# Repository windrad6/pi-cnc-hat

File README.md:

https://www.digikey.de/de/products/detail/edac-inc/630-025-640-541/10867386

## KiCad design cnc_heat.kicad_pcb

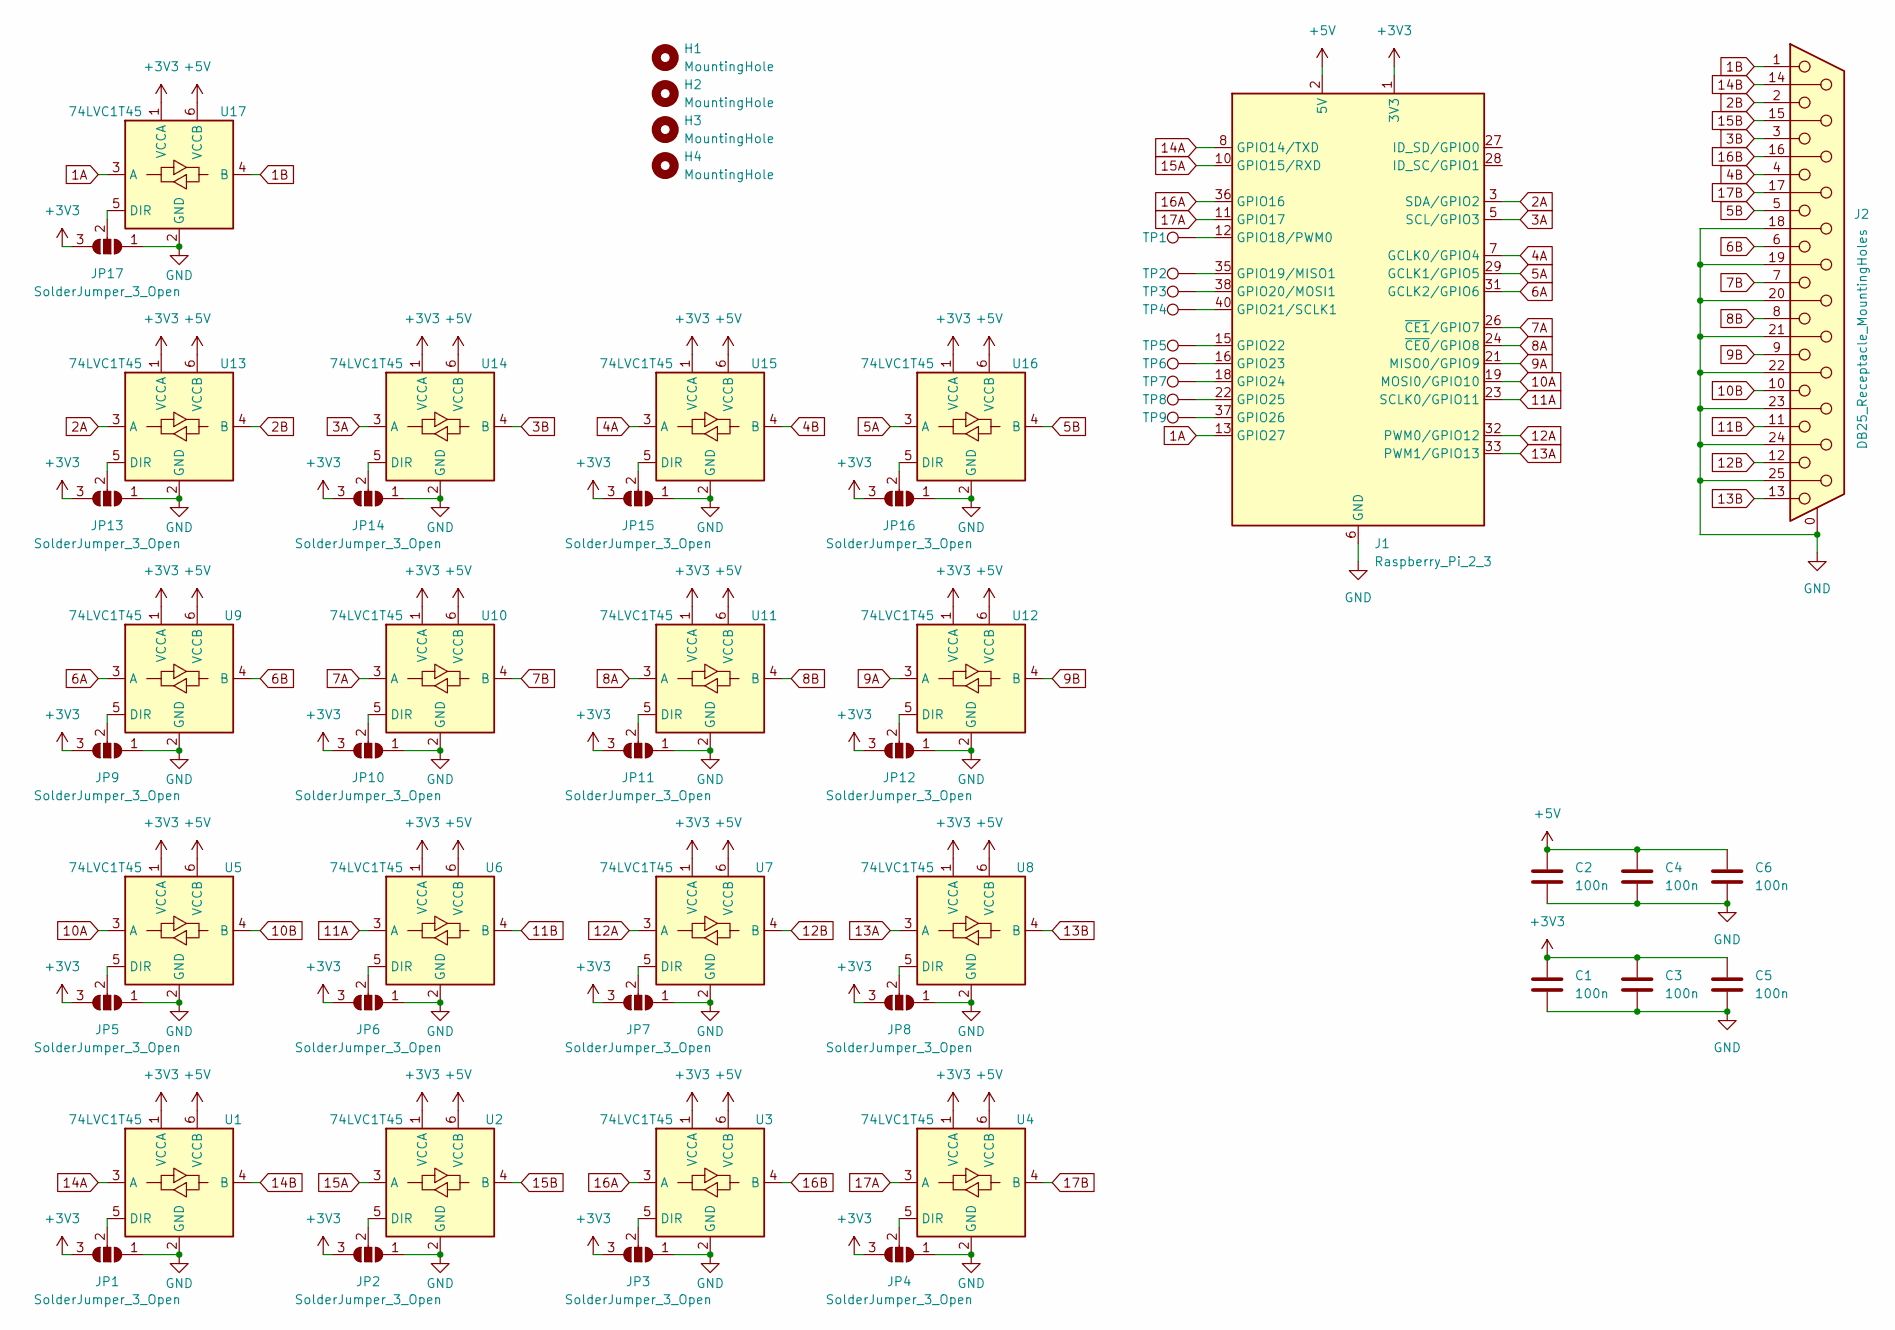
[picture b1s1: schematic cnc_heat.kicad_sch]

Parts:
C1, C2, C3, C4, C5, C6: 100n; C_1206_3216Metric_Pad1.33x1.80mm_HandSolder
H1, H2, H3, H4: MountingHole; MountingHole_2.7mm_M2.5
J1: Raspberry_Pi_2_3; PinSocket_2x20_P2.54mm_Vertical
J2: DB25_Receptacle_MountingHoles; DSUB-25_Female_Horizontal_P2.77x2.84mm_EdgePinOffset9.90mm_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; DIGIKEY 151-630-025-640-541-ND
JP1, JP2, JP3, JP4, JP5, JP6, JP7, JP8, JP9, JP10, JP11, JP12, JP13, JP14, JP15, JP16, JP17: SolderJumper_3_Open; SolderJumper-3_P2.0mm_Open_TrianglePad1.0x1.5mm_NumberLabels
TP1, TP2, TP3, TP4, TP5, TP6, TP7, TP8, TP9: TestPoint; TestPoint_Pad_1.5x1.5mm
U1, U2, U3, U4, U5, U6, U7, U8, U9, U10, U11, U12, U13, U14, U15, U16, U17: 74LVC1T45; SOT-23-6; DIGIKEY 74LVC1T45W6-7

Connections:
1A: J1.13 (GPIO27), U17.3 (A)
1B: J2.1, U17.4 (B)
2A: J1.3 (SDA/GPIO2), U13.3 (A)
2B: J2.2, U13.4 (B)
3A: J1.5 (SCL/GPIO3), U14.3 (A)
3B: J2.3, U14.4 (B)
4A: J1.7 (GCLK0/GPIO4), U15.3 (A)
4B: J2.4, U15.4 (B)
5A: J1.29 (GCLK1/GPIO5), U16.3 (A)
5B: J2.5, U16.4 (B)
6A: J1.31 (GCLK2/GPIO6), U9.3 (A)
6B: J2.6, U9.4 (B)
7A: J1.26 (~CE1/GPIO7), U10.3 (A)
7B: J2.7, U10.4 (B)
8A: J1.24 (~CE0/GPIO8), U11.3 (A)
8B: J2.8, U11.4 (B)
9A: J1.21 (MISO0/GPIO9), U12.3 (A)
9B: J2.9, U12.4 (B)
10A: J1.19 (MOSI0/GPIO10), U5.3 (A)
10B: J2.10, U5.4 (B)
11A: J1.23 (SCLK0/GPIO11), U6.3 (A)
11B: J2.11, U6.4 (B)
12A: J1.32 (PWM0/GPIO12), U7.3 (A)
12B: J2.12, U7.4 (B)
13A: J1.33 (PWM1/GPIO13), U8.3 (A)
13B: J2.13, U8.4 (B)
14A: J1.8 (GPIO14/TXD), U1.3 (A)
14B: J2.14, U1.4 (B)
15A: J1.10 (GPIO15/RXD), U2.3 (A)
15B: J2.15, U2.4 (B)
16A: J1.36 (GPIO16), U3.3 (A)
16B: J2.16, U3.4 (B)
17A: J1.11 (GPIO17), U4.3 (A)
17B: J2.17, U4.4 (B)
+3V3: C1.1, C3.1, C5.1, J1.1 (3V3), J1.17 (3V3), JP1.3 (B), JP2.3 (B), JP3.3 (B), JP4.3 (B), JP5.3 (B), JP6.3 (B), JP7.3 (B), JP8.3 (B), JP9.3 (B), JP10.3 (B), JP11.3 (B), JP12.3 (B), JP13.3 (B), JP14.3 (B), JP15.3 (B), JP16.3 (B), JP17.3 (B), U1.1 (VCCA), U2.1 (VCCA), U3.1 (VCCA), U4.1 (VCCA), U5.1 (VCCA), U6.1 (VCCA), U7.1 (VCCA), U8.1 (VCCA), U9.1 (VCCA), U10.1 (VCCA), U11.1 (VCCA), U12.1 (VCCA), U13.1 (VCCA), U14.1 (VCCA), U15.1 (VCCA), U16.1 (VCCA), U17.1 (VCCA)
+5V: C2.1, C4.1, C6.1, J1.2 (5V), J1.4 (5V), U1.6 (VCCB), U2.6 (VCCB), U3.6 (VCCB), U4.6 (VCCB), U5.6 (VCCB), U6.6 (VCCB), U7.6 (VCCB), U8.6 (VCCB), U9.6 (VCCB), U10.6 (VCCB), U11.6 (VCCB), U12.6 (VCCB), U13.6 (VCCB), U14.6 (VCCB), U15.6 (VCCB), U16.6 (VCCB), U17.6 (VCCB)
GND: C1.2, C2.2, C3.2, C4.2, C5.2, C6.2, J1.6 (GND), J1.9 (GND), J1.14 (GND), J1.20 (GND), J1.25 (GND), J1.30 (GND), J1.34 (GND), J1.39 (GND), J2.0 (PAD), J2.18, J2.19, J2.20, J2.21, J2.22, J2.23, J2.24, J2.25, JP1.1 (A), JP2.1 (A), JP3.1 (A), JP4.1 (A), JP5.1 (A), JP6.1 (A), JP7.1 (A), JP8.1 (A), JP9.1 (A), JP10.1 (A), JP11.1 (A), JP12.1 (A), JP13.1 (A), JP14.1 (A), JP15.1 (A), JP16.1 (A), JP17.1 (A), U1.2 (GND), U2.2 (GND), U3.2 (GND), U4.2 (GND), U5.2 (GND), U6.2 (GND), U7.2 (GND), U8.2 (GND), U9.2 (GND), U10.2 (GND), U11.2 (GND), U12.2 (GND), U13.2 (GND), U14.2 (GND), U15.2 (GND), U16.2 (GND), U17.2 (GND)
unnamed: J1.12 (GPIO18/PWM0), TP1.1
unnamed: J1.35 (GPIO19/MISO1), TP2.1
unnamed: J1.38 (GPIO20/MOSI1), TP3.1
unnamed: J1.40 (GPIO21/SCLK1), TP4.1
unnamed: J1.15 (GPIO22), TP5.1
unnamed: J1.16 (GPIO23), TP6.1
unnamed: J1.18 (GPIO24), TP7.1
unnamed: J1.22 (GPIO25), TP8.1
unnamed: J1.37 (GPIO26), TP9.1
unnamed: JP1.2 (C), U1.5 (DIR)
unnamed: JP2.2 (C), U2.5 (DIR)
unnamed: JP3.2 (C), U3.5 (DIR)
unnamed: JP4.2 (C), U4.5 (DIR)
unnamed: JP5.2 (C), U5.5 (DIR)
unnamed: JP6.2 (C), U6.5 (DIR)
unnamed: JP7.2 (C), U7.5 (DIR)
unnamed: JP8.2 (C), U8.5 (DIR)
unnamed: JP9.2 (C), U9.5 (DIR)
unnamed: JP10.2 (C), U10.5 (DIR)
unnamed: JP11.2 (C), U11.5 (DIR)
unnamed: JP12.2 (C), U12.5 (DIR)
unnamed: JP13.2 (C), U13.5 (DIR)
unnamed: JP14.2 (C), U14.5 (DIR)
unnamed: JP15.2 (C), U15.5 (DIR)
unnamed: JP16.2 (C), U16.5 (DIR)
unnamed: JP17.2 (C), U17.5 (DIR)

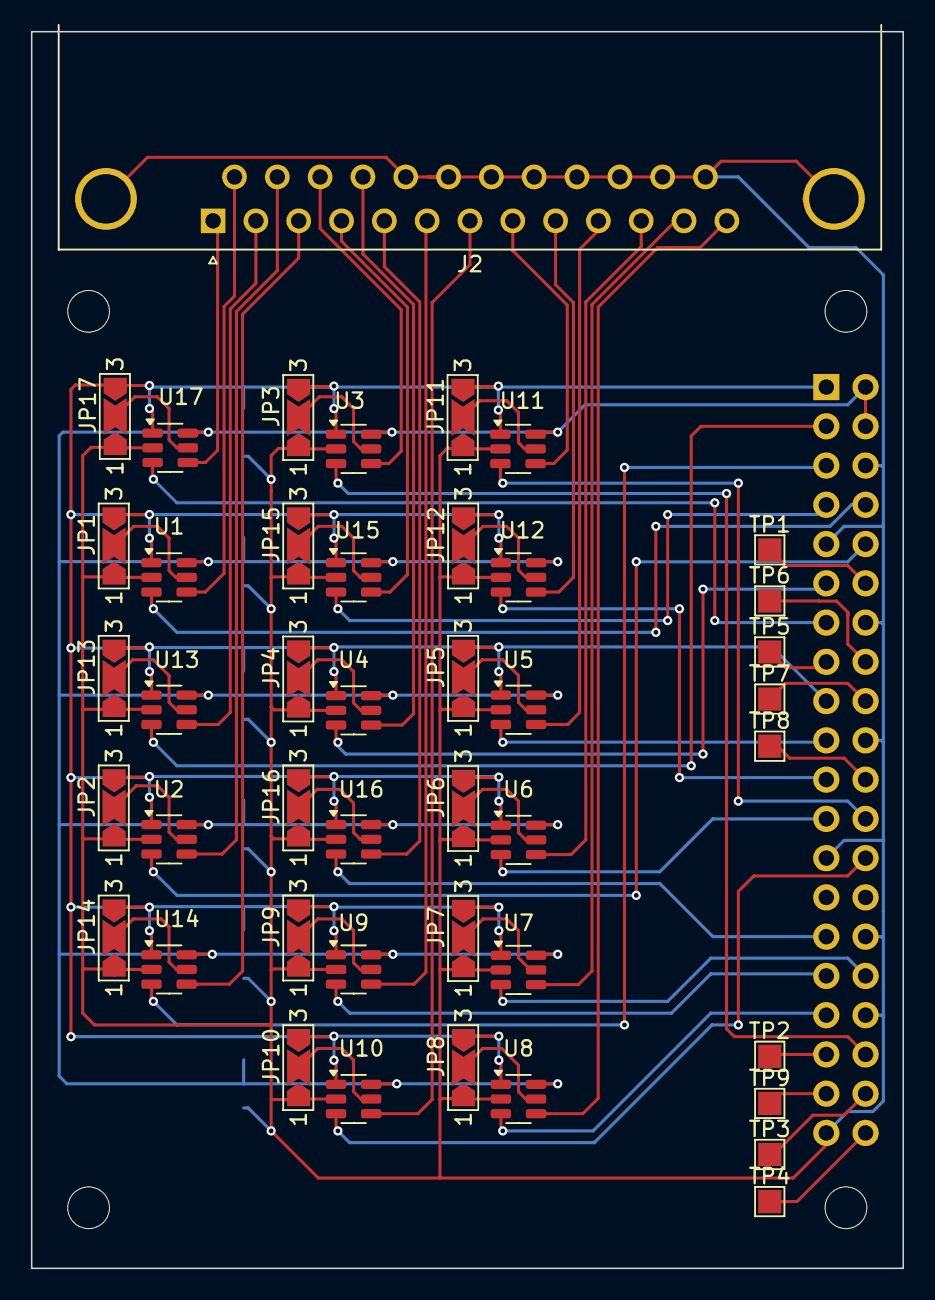
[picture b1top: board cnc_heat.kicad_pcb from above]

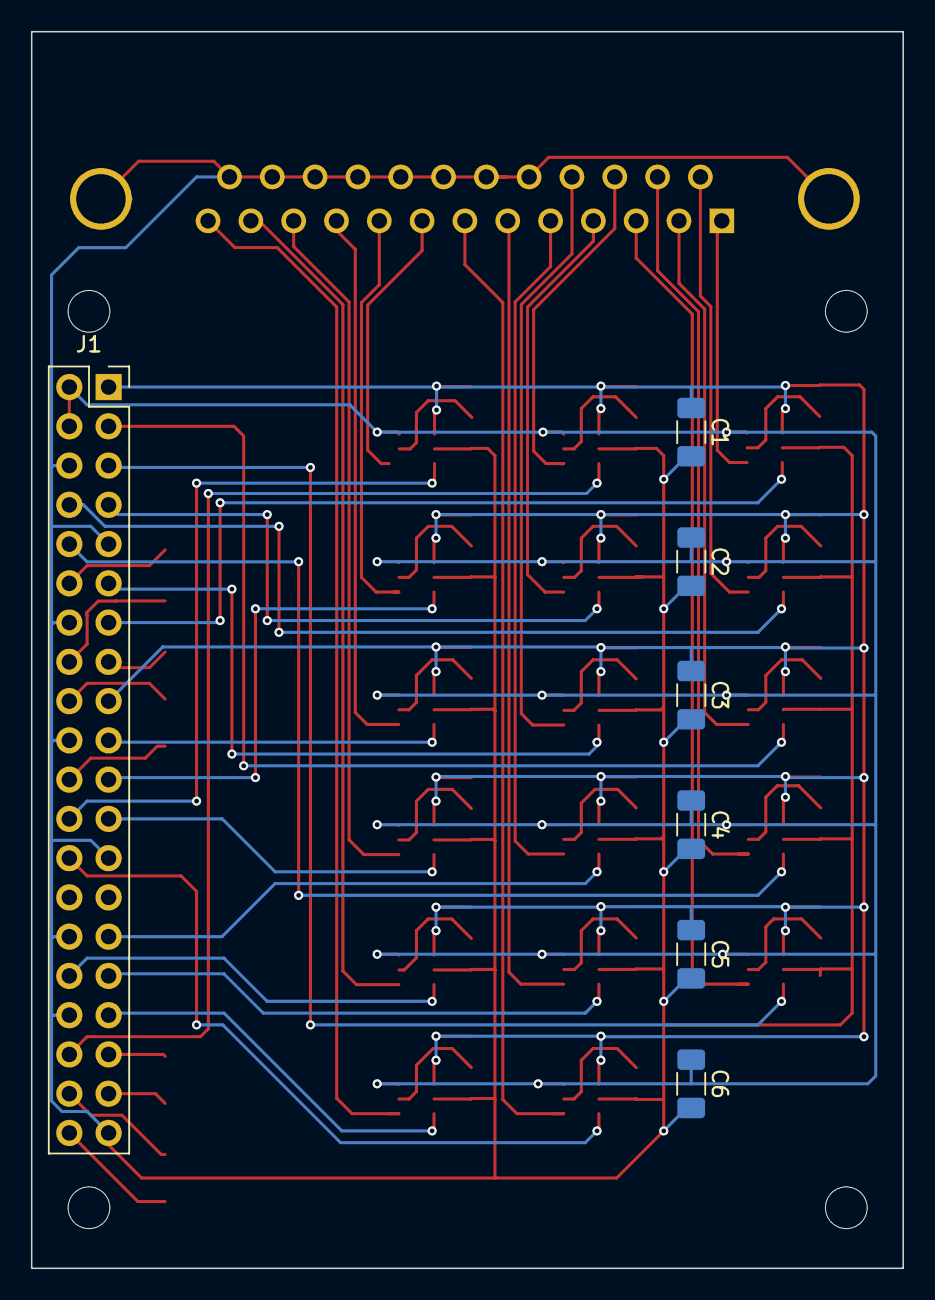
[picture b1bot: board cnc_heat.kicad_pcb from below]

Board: 2 copper layers, 56.4 x 80.0 mm, 55 parts (7 on the bottom side), 63 nets.

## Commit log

2024-06-30 inital version of pcb and schematic
2024-06-30 routing cleanup
2024-07-01 ocd routing
